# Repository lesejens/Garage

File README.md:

# Garage
Arduino based I/O-controller using configurable to connect to FHEM. TEst

24VDC Power Supply required

8 Digital Inputs (24VDC/Optocoupler)

8 Digital Outputs (24VDC/ULN2891)

1 Wire-Bus

DIN-Rail Housing

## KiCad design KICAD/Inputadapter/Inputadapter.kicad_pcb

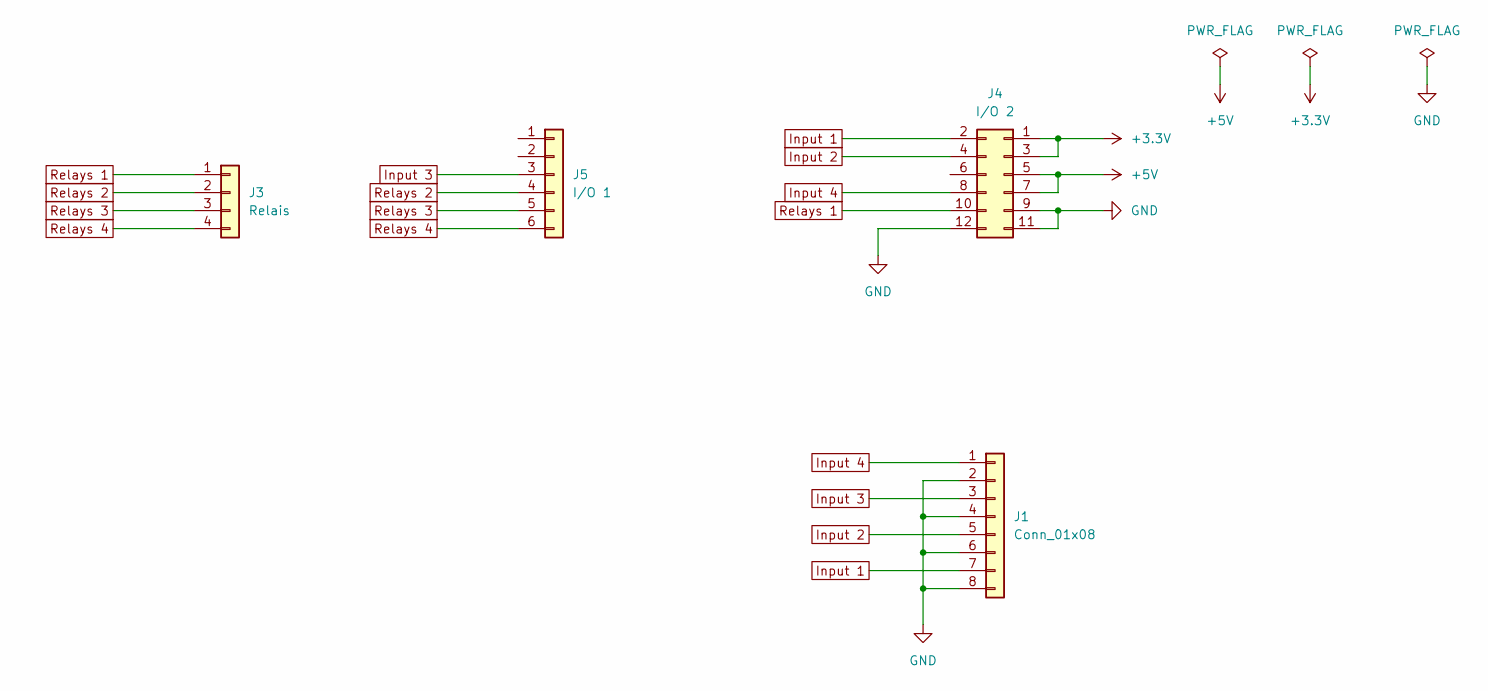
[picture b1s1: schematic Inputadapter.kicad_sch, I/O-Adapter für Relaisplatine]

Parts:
J1: Conn_01x08; PhoenixContact_MSTBVA_2,5_8-G-5,08_1x08_P5.08mm_Vertical
J3: Relais; PinHeader_1x04_P2.54mm_Vertical
J4: I/O 2; PinHeader_2x06_P2.54mm_Vertical
J5: I/O 1; PinHeader_1x06_P2.54mm_Vertical

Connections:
+3V3: J4.1, J4.3
+5V: J4.5, J4.7
GND: J1.2, J1.4, J1.6, J1.8, J4.9, J4.11, J4.12
Input 1: J1.7, J4.2
Input 2: J1.5, J4.4
Input 3: J1.3, J5.3
Input 4: J1.1, J4.8
Relays 1: J3.1, J4.10
Relays 2: J3.2, J5.4
Relays 3: J3.3, J5.5
Relays 4: J3.4, J5.6

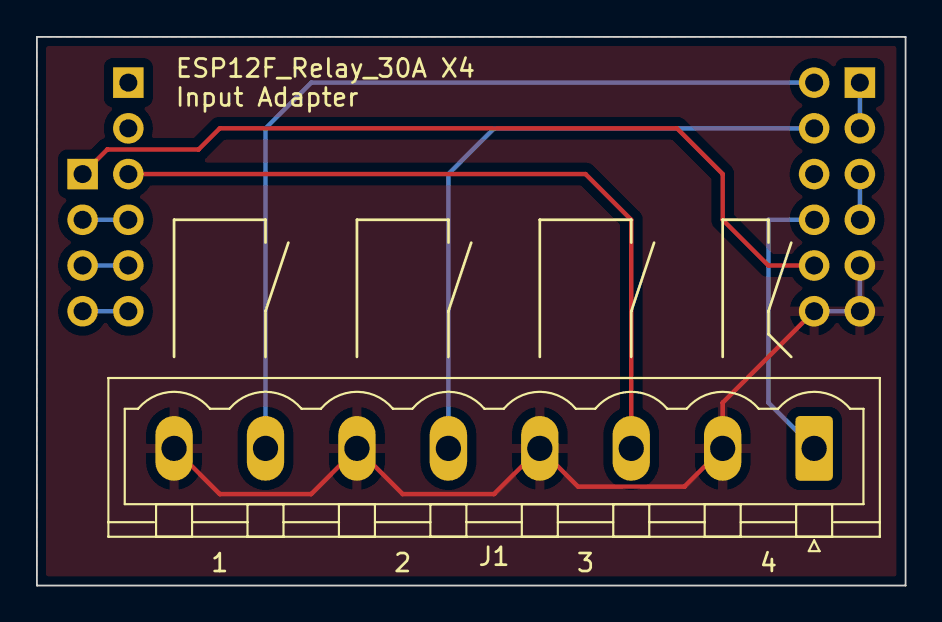
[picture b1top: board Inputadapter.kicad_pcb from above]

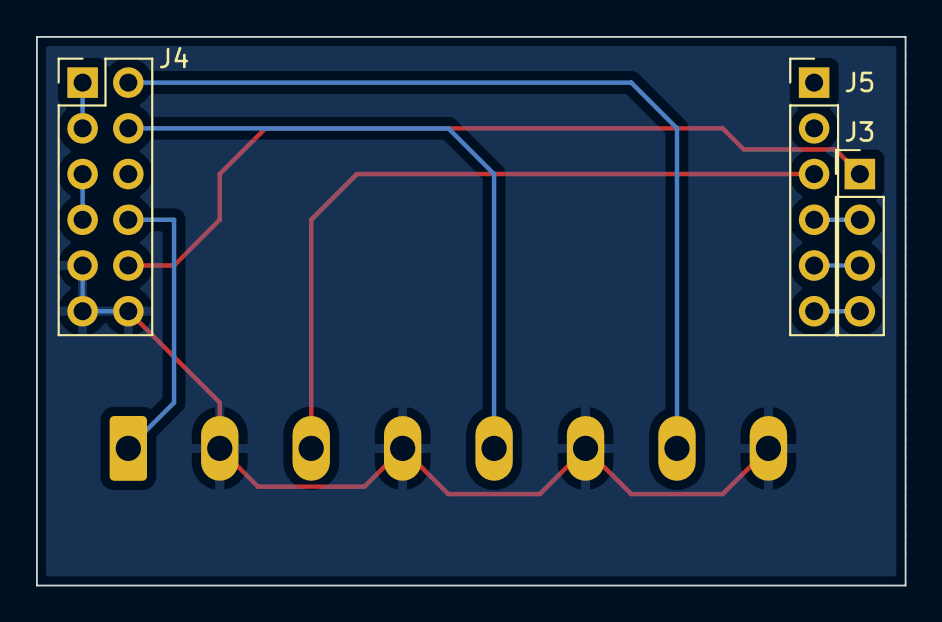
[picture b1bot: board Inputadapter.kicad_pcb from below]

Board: 2 copper layers, 48.3 x 30.5 mm, 4 parts (3 on the bottom side), 11 nets.

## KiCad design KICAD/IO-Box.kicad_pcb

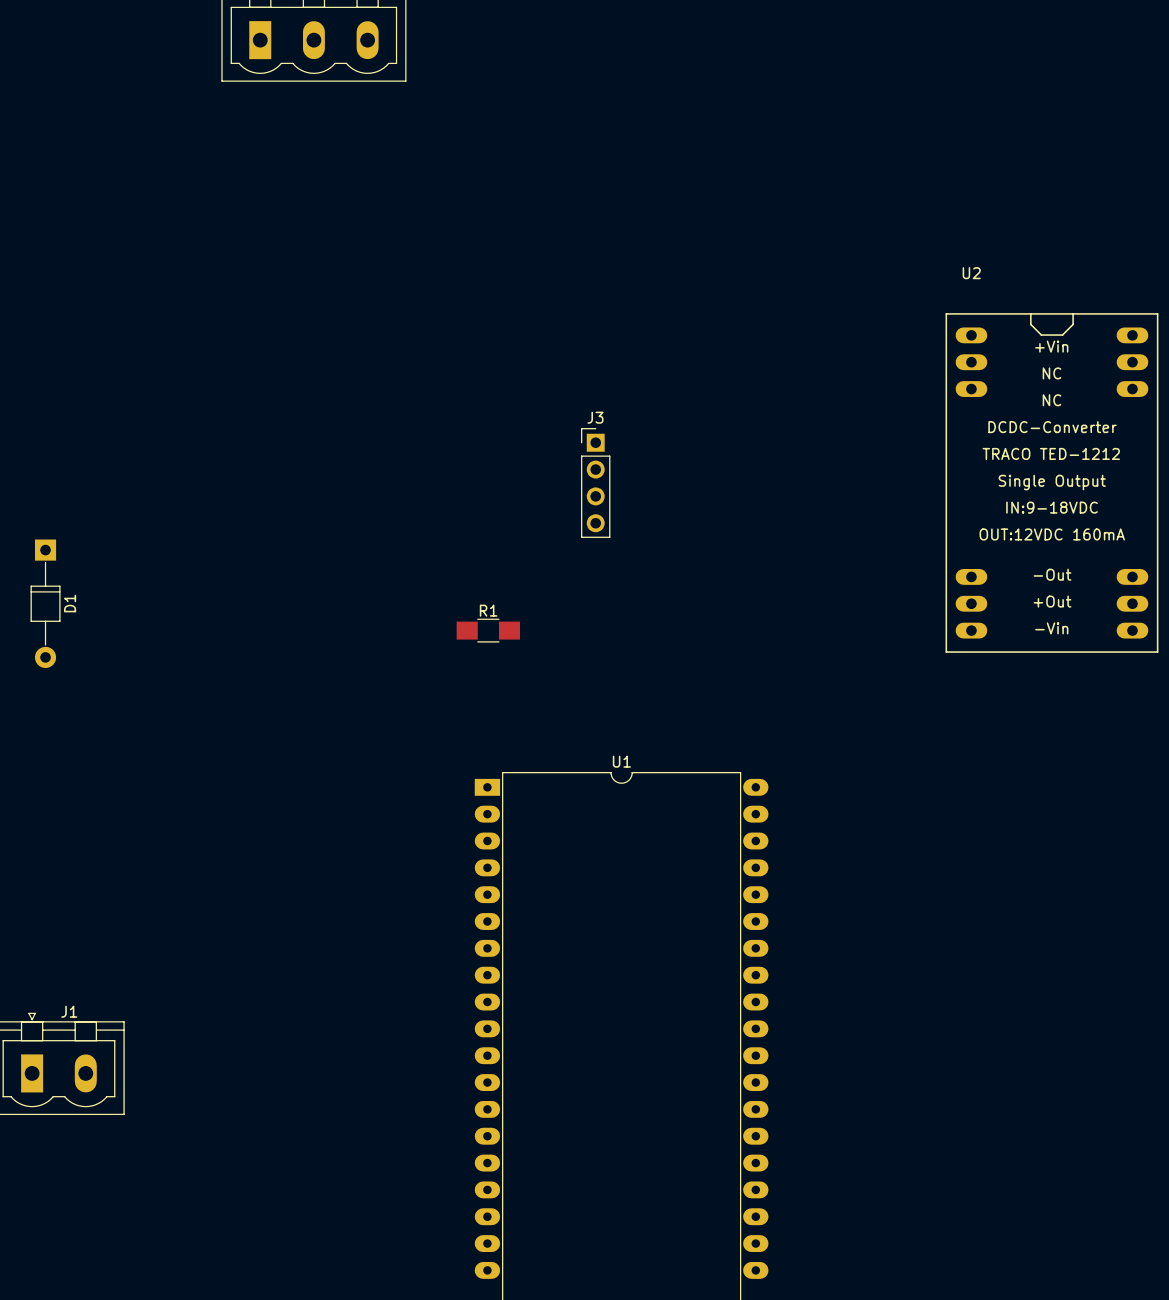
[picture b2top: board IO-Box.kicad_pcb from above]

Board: 2 copper layers, 7 parts (0 on the bottom side), 7 nets, no tracks yet.

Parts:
D1: 1N4148; D_T-1_P10.16mm_Horizontal
J1: Power In; PhoenixContact_MSTBVA-G_02x5.08mm_Vertical
J2: 1WireBus; PhoenixContact_MSTBVA-G_03x5.08mm_Vertical
J3: Conn_01x04; Pin_Header_Straight_1x04_Pitch2.54mm
R1: 4k7; R_1206_HandSoldering
U1: ESP32-DevKitC; DIP-38_W25.4mm_LongPads
U2: DC/DC-Converter; DCDC-Conv_TRACO_TED-1212_Single_9-18VDCto12VDC160mA

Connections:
/1W: J2.2, R1.1, U1.24
/SCL: J3.3, U1.36
/SDA: J3.4, U1.33
GND: J1.1, J2.1, J3.1, U1.14, U1.32, U1.38, U2.10, U2.12, U2.13, U2.15
unnamed: D1.1, U2.1, U2.24
unnamed: D1.2, J1.2
VCC: J2.3, R1.2, U1.19, U2.11, U2.14

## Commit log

2015-05-27 Test
2015-06-01 Arduino Core added
2015-06-05 Ersterstellung
2015-06-12 Neue Boards
2015-06-12 Neuen Nano eingebaut.
2015-06-17 DCDC-Converter added
2015-06-19 Optokoppler eingefügt
2015-06-19 Layout
2015-06-30 Neuer Laptop, weiter gehts ...
2015-07-01 Layout 1.0 beendet
2015-08-02 Stromlaufplan aufgehübscht.
2015-11-17 Creation of Label
2016-04-29 Lochabstände angepasst.
2016-06-03 Weiß nicht was ...
2017-09-23 Switch to ESP32 + KICAD
2017-09-23 Hardware deleted --> Move to KICAD
2019-10-27 Commit Test
2022-04-08 Testcommit
2022-04-08 Another test
2022-04-10 Take ovr of local file.
